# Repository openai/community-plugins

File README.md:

# Community Plugins

A public, Git-backed marketplace of Codex plugins that developers, prospects,
and enterprise teams can inspect before they install. Each plugin is packaged
with its manifest, setup guide, tests, and license or third-party notices.

The CDE team stewards this collection of public plugins for enterprise use
cases. CDE maintainers review contributions and provide support through
repository issues on a best-effort basis; this
repository does not provide an enterprise support commitment or service-level
agreement.

Inclusion in OpenAI's official Plugins Directory requires a separate review. See
[OpenAI's plugin packaging docs](https://developers.openai.com/plugins/build/plugins)
for the distinction between public directory publishing and repo marketplaces.

## Add it to Codex

In Codex, choose **Add plugin marketplace** and use a repository slug or clone
URL, not a raw `marketplace.json` URL:

```text
Source: tonyloehr/community-plugins
Git ref: main
Sparse paths:
.agents/plugins
plugins
```

Those two sparse paths load the complete plugin catalog without pulling the
top-level test suites or demo media. Package-owned source, contract fixtures,
licenses and build receipts remain included. To fetch every repository file,
leave **Sparse paths** blank. To fetch only Grafana Observability, use these two
paths instead:

```text
.agents/plugins
plugins/grafana-observability
```

To fetch only ReviewOps Auditor + Benchmark, use:

```text
.agents/plugins
plugins/reviewops-auditor-benchmark
```

To fetch only React Native to SwiftUI, use:

```text
.agents/plugins
plugins/react-native-to-swiftui
```

To fetch only Autodesk Fusion interoperability, use:

```text
.agents/plugins
plugins/autodesk-fusion
```

To fetch the Physical Engineering candidate, use:

```text
.agents/plugins
plugins/physical-engineering
```

Adding a marketplace makes its catalog available to browse. It does **not**
install, enable, or authenticate every plugin. After adding it, install only
the plugin you want.

The same flow from the CLI:

```sh
# Load the full catalog efficiently.
codex plugin marketplace add tonyloehr/community-plugins \
  --ref main \
  --sparse .agents/plugins \
  --sparse plugins

# Install one plugin from that catalog.
codex plugin add grafana-observability@community-plugins

# Or install the offline ReviewOps package.
codex plugin add reviewops-auditor-benchmark@community-plugins

# Or install the bounded native-migration workflow.
codex plugin add react-native-to-swiftui@community-plugins

# Or install the Fusion interoperability preview (starts in synthetic fixture mode).
codex plugin add autodesk-fusion@community-plugins

# Or install the reusable mechanical CAD workflow and examples.
codex plugin add physical-engineering@community-plugins
```

If you want a full checkout instead of a sparse one:

```sh
codex plugin marketplace add tonyloehr/community-plugins --ref main
```

The `@community-plugins` selector comes from the top-level `name` in
[the marketplace manifest](.agents/plugins/marketplace.json), not from the
GitHub URL. Start a new Codex task after installation so its skills and tools
are picked up.

## Available plugins

| Plugin                                                                         | Purpose                                                                                                                    | Learn more                                                                                                                |
| ------------------------------------------------------------------------------ | -------------------------------------------------------------------------------------------------------------------------- | ------------------------------------------------------------------------------------------------------------------------- |
| [Grafana Observability](plugins/grafana-observability/README.md)               | Inspect administrator-approved, read-only Grafana evidence for infrastructure, APM, logs, IoT/edge, and business KPIs.     | [Guide](plugins/grafana-observability/README.md) · [23-second demo](docs/media/grafana-production-monitoring-demo-8x.mp4) |
| [ReviewOps Auditor + Benchmark](plugins/reviewops-auditor-benchmark/README.md) | Normalize sanitized review-run exports, audit evaluation validity, benchmark lanes, and emit shadow-only guidance offline. | [Guide](plugins/reviewops-auditor-benchmark/README.md)                                                                    |
| [React Native to SwiftUI](plugins/react-native-to-swiftui/README.md)           | Plan a bounded React Native/Expo feature migration, then port one explicitly approved slice with deterministic SwiftUI parity checks. | [Guide](plugins/react-native-to-swiftui/README.md) |
| [Autodesk Fusion](plugins/autodesk-fusion/README.md) | Connect typed CAD/CAM operations, scoped Autodesk data, reviewed cloud recipes and engineering evidence; live qualification required. | [Guide](plugins/autodesk-fusion/README.md) |
| [Physical Engineering](plugins/physical-engineering/README.md) | Build mechanical CAD from a brief, measure exports, preserve revisions and deliver a repeatable handoff. Custom parts plus a drone assembly example. Preview. | [Guide](plugins/physical-engineering/README.md) · [Two-minute demo](docs/media/physical-engineering/README.md) · [Session runbook](docs/physical-engineering-demo-runbook.md) |
| [PCBA Engineering](plugins/pcba-engineering/README.md) | Reconcile assembly data, apply bounded revisions, and independently verify an offline PCBA handoff. | [Guide](plugins/pcba-engineering/README.md) · [2:27 demo](docs/media/pcba-engineering/README.md) |
| [AI/ML API](plugins/aimlapi/README.md) | Choose models and build chat, media, speech, batch, webhook and sandbox integrations with 13 upstream skills. | [Guide](plugins/aimlapi/README.md) |

Grafana Observability requires Codex and Node.js 22.19 or newer. Its manifest
declares both `Read` and `Write`. `Write` is limited to
plugin-owned local audit and evidence files; it does not write to Grafana,
datasources, dashboards, services, or deployments.

Its default startup uses a credential-free fixture, so you can verify the
install without touching a Grafana instance:

```text
Use $setup-grafana-observability to check the fixture profile and available packs.
```

ReviewOps Auditor + Benchmark requires Codex and Node.js 22.19 or newer. Its
manifest declares only `Read`; it has no app, MCP server, authentication,
network call, model replay, workflow execution, or writeback path. Its first
run is also synthetic and credential-free:

```text
Use $normalize-review-runs on the bundled synthetic fixture only. Explain the normalization summary, provenance checks, safety boundaries, and next safe step.
```

React Native to SwiftUI requires Codex and Node.js 22.19 or newer. Its
manifest declares both `Read` and `Write`: planning is read-only, while
writes are limited to an explicitly approved target directory for one feature
slice. It has no app or MCP dependency, does not copy source or assets into
the plugin, and does not promise App Store approval. Its first run is a
read-only parity-planning prompt:

```text
Use $plan-react-native-port to inspect only the declared React Native feature and propose a SwiftUI parity contract. Do not edit files yet.
```

Autodesk Fusion requires Codex and Node.js 22.19 or newer. It declares `Read`
and `Write` for scoped desktop changes, local evidence and configured Autodesk
cloud operations. Authentication is `ON_USE`: the initial synthetic fixture
requires no Autodesk account or running Fusion process. Real desktop, cloud and
manufacturing use requires the appropriate license, profile, authority and
independent qualification; installation grants none of these.

```text
Use $setup-autodesk-fusion to check the synthetic fixture and explain the available connection modes. Do not connect to Autodesk or change a real model.
```

Physical Engineering targets macOS arm64 with Python 3.14 and separately
installed Text-to-CAD 0.10.3. It declares `Read` and `Write` for the selected
local study, runtime and handoff. Custom single-solid parts use declared
measurements; the drone assembly is an optional specialized example. Neither
needs a CAD account. Setup downloads public dependencies, and Codex uses the
user's configured model provider. Digital checks do not qualify fabrication.

```text
Use $engineer-subsystem to start a mechanical-part study from my brief in an empty directory. Record supported measurements and unresolved requirements, then build and check the CAD.
```

## Copy-paste Codex prompts

Browse before installing:

```text
Add the Git-backed marketplace from tonyloehr/community-plugins at ref main. Use sparse paths .agents/plugins and plugins. List the available plugins and recommend the best fit for this repository, but do not install or authenticate anything yet.
```

Install one plugin:

```text
If community-plugins is not already configured, add it from tonyloehr/community-plugins at ref main using sparse paths .agents/plugins and plugins/grafana-observability. Install grafana-observability@community-plugins, explain its permissions and authentication policy, and give me the credential-free smoke-test prompt for a new Codex task.
```

Install ReviewOps without private data:

```text
If community-plugins is not already configured, add it from tonyloehr/community-plugins at ref main using sparse paths .agents/plugins and plugins/reviewops-auditor-benchmark. Install reviewops-auditor-benchmark@community-plugins, explain its read-only offline boundary, and give me the synthetic-fixture smoke-test prompt for a new Codex task.
```

Install React Native to SwiftUI with a read-only first run:

```text
If community-plugins is not already configured, add it from tonyloehr/community-plugins at ref main using sparse paths .agents/plugins and plugins/react-native-to-swiftui. Install react-native-to-swiftui@community-plugins, explain its Read and Write boundaries and ON_USE authentication policy, and give me the read-only parity-planning prompt for a new Codex task.
```

Review before adoption:

```text
Review tonyloehr/community-plugins before I install it. Inspect .agents/plugins/marketplace.json, each plugin manifest, declared capabilities, authentication policy, external endpoints, licenses, and setup instructions. Flag anything that needs security or admin review.
```

## Update or remove

```sh
# Refresh the Git-backed marketplace snapshot.
codex plugin marketplace upgrade community-plugins

# Reinstall a plugin after a new version is published.
codex plugin add grafana-observability@community-plugins
codex plugin add reviewops-auditor-benchmark@community-plugins
codex plugin add react-native-to-swiftui@community-plugins
codex plugin add autodesk-fusion@community-plugins

# Remove the configured marketplace source.
codex plugin marketplace remove community-plugins
```

For an enterprise fork or private mirror, use its HTTPS or SSH clone URL and
make sure Git credentials already work non-interactively. Keep the same
`.agents/plugins/marketplace.json` and `plugins/<name>/` layout.

## Repository layout

Plugin master suites follow `npm run test:<plugin-name>` and are discovered by
`npm run test:marketplace`. Fusion's companion tests live under
[`tests/autodesk-fusion`](tests/autodesk-fusion/README.md), grouped into unit,
integration and security checks. The cold package suite needs no development
dependencies; the full master also rebuilds and runs the deeper Node/Python
contracts:

```sh
npm run test:autodesk-fusion:package
npm --prefix plugins/autodesk-fusion ci --ignore-scripts
npm run test:autodesk-fusion
```

Python 3.12 or newer is required for Fusion's development contract suite, not
for normal Codex startup. The test guide distinguishes synthetic, licensed,
installed-client and native-credential checks; a skipped gate is not a pass.

```text
.agents/plugins/marketplace.json      # Catalog and install policy
plugins/<plugin-name>/                 # One installable plugin
  .codex-plugin/plugin.json            # Required plugin manifest
  README.md                            # Cold-start setup and safety guidance
tests/<plugin-name>/                   # Plugin-specific verification
scripts/                               # Marketplace and package checks
```

## Trust and contributions

Treat every plugin as code you are choosing to run. Review its manifest,
capabilities, authentication policy, setup guide, and license before installing
it. This repository never needs credentials committed to it.

See [CONTRIBUTING.md](CONTRIBUTING.md) to add or update a plugin,
[SECURITY.md](SECURITY.md) to report a vulnerability, and
[CODE_OF_CONDUCT.md](CODE_OF_CONDUCT.md) for participation expectations. The
repository is Apache-2.0 licensed; individual plugins may carry their own
license and third-party notices.

External contributions use pull requests from forks. CDE code owners review
the latest changes, and contributions must satisfy the CLA, test, and security
requirements before merging. Maintainers follow the
[repository access and merge policy](docs/maintainer-guide.md).

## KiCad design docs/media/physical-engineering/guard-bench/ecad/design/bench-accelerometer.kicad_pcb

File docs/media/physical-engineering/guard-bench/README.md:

# Rebuild the guard-coupon bench

An indoor 65 mm quad has two candidate guard walls, 1.00 and 1.40 mm. This companion includes the revised aircraft, two separate printable specimens, a keyed test fixture and a custom three-axis recorder. The nominal tip-to-stop displacement is 2.00 mm for either specimen. Build the virtual station, then compare the enclosure, board and fixture in their installed positions. Measuring acceleration or ring-down requires physical hardware.

## Present the demo

Play the [silent 6:24 stage film](https://github.com/user-attachments/assets/fb31f2b8-419d-4036-bfda-f1f37bc846d7) and follow the [timed reader](presenting/Presenter-runbook.html) on a second screen. Download the HTML reader for its rehearsal controls, or use the [printable PDF](presenting/Presenter-runbook.pdf) and [Markdown script](presenting/Presenter-runbook.md). The narrated edition is on [PR #61](https://github.com/openai/community-plugins/pull/61). Download and open the [standalone HTML prompt deck](presenting/Prompt-runbook.html) for the copy buttons, or use the [plain-text prompts](presenting/Prompt-runbook.md).

A separate 561-second Desktop turn started with an empty output directory and authored its own accelerometer PCB. Its J1.3–U1.6 SDA route measured 5.1534 mm on front copper with zero vias. KiCad reported zero ERC findings, DRC findings, unconnected items and schematic-parity findings. The reviewed film board takes 7.393 mm and two vias between the same pins. The source replay below reproduces the reviewed board. [Independent Desktop board readback](evidence/desktop-board.json)

## Replay from editable source

Start at the repository root. The replay creates a new directory. It generates the populated board from its native KiCad project, uses that fresh STEP for the housing and combines the delivered housing and fixture. Each of the three Physical Engineering handoffs also rebuilds from its own source in a second directory. Set up the CAD runtime with Python 3.14 and uv once. [Physical Engineering setup](../../../../plugins/physical-engineering/references/assembly-designs.md)

```sh
export PE_RUNTIME="${PE_RUNTIME:-$HOME/.cache/physical-engineering/runtime}"
if [ ! -x "$PE_RUNTIME/bin/python" ]; then
  python3 plugins/physical-engineering/scripts/engineering.py setup --runtime "$PE_RUNTIME"
fi

companion=docs/media/physical-engineering/guard-bench
docker build -t physical-engineering-kicad:9.0.2 "$companion/ecad"
python3 "$companion/replay.py" ./guard-bench-replay --kicad-image physical-engineering-kicad:9.0.2
```

A native KiCad 9.0.2 installation with matching stock symbol/footprint libraries, `kicad-cli` on PATH and Python bindings for `pcbnew` also works with the same command after removing the image argument. If necessary, set `KICAD_PYTHON` to the interpreter containing `pcbnew`. The Docker run uses the local image with networking disabled after setup. The final `replay.json` contains the results and baseline/rebuild manifest digests.

| Output under the replay directory | What to open |
| --- | --- |
| `aircraft/` | Complete STEP, colored GLB, print meshes, offline viewer, formatted aircraft/bench BOM, board guide and flight-controller thickness readback |
| `board/` | Native project with local models, rendered schematic PDF, ERC, parity-aware DRC, netlist, placements, parts list, nine Gerber layers, plated/non-plated drills and populated STEP |
| `fixture/` | Assembly with one 1.00 mm specimen, keyed stop and an enclosure reference. The alternate directory contains the installed 1.40 mm specimen and its separate print. |
| `housing/` | Enclosure positioned around the freshly exported, populated recorder. The installed board contains discrete substrate, copper, pad, via and packaged-part geometry. |
| `station/` | Integrated STEP, GLB and a registration report. The real recorder assembly replaces the two enclosure reference bodies. |
| `aircraft-rebuild/`, `fixture-rebuild/`, `housing-rebuild/` | Independent rebuilds from each handoff’s delivered source |
| `housing-regression/exports/integration.json` | Rejected enclosure copy with the earlier 15 × 3 mm opening. The cable gauge intersects 28.70 mm³ of the wall. |
| `board/edge-regression-drc.json` | Separate rejected source copy with the connector moved 0.25 mm toward the edge |

The [full system workbook](sourcing/system-bom.xlsx) consolidates aircraft, both specimen configurations, the recorder PCB and workshop equipment. Its six sheets reconcile 69 source entries into 59 distinct rows. The two coupon columns represent alternative assemblies and shared fixture fasteners are counted once. [Flat CSV](sourcing/system-bom.csv) · [Reconciliation](sourcing/reconciliation.json)

## Engineering decisions

| Interface | Source decision and digital evidence | Physical work |
| --- | --- | --- |
| Aircraft controller | The BETAFPV Air 5IN1 specifies a 0.80 mm substrate. The earlier STEP measured 0.95 mm. The revised model holds the lower face at Z 3.50 mm and seats its upper components at 4.30 mm. | Check the received revision, compressed grommets, screw engagement and harness routing. [Controller specification](https://betafpv.com/products/air-brushless-flight-controller?variant=41142912745606) |
| Motor connection | The 0702SE II leads ship with connectors. The selected controller takes soldered motor wires. The workbook records lead termination and kit inclusions. | Confirm finished lengths, strain relief, prop fit and propulsion load. [Motor specification](https://betafpv.com/products/0702-ii-brushless-motors?variant=41478718750854) |
| Recorder board | An ST LIS3DHTR and side-entry JST SH connector share the 34 × 22 mm board. A 3.3 V host supplies power and reads I²C at address 0x18. The two-layer SDA route from J1.3 to U1.6 measures 7.393 mm and changes layers twice. | Fabricate, inspect orientation and electrical joints, verify identity and gravity response. [ST datasheet](https://www.st.com/resource/en/datasheet/lis3dh.pdf) · [JST drawing](https://www.jst-mfg.com/product/pdf/eng/eSH.pdf) |
| Connector hold-downs | KiCad requires 0.50 mm copper-to-edge clearance. Moving J1 inward 0.25 mm gives both hold-down pads 0.60 mm. The replay moves J1 back in a copy and requires both 0.35 mm violations. Moving an already-routed footprint also triggers other layout findings recorded in that copy. | Check actual fit and fabrication tolerances. |
| Recorder mounting | The housing uses a 64 mm ear spacing and checks the populated board against the lid, four mounts, screws and cable entry. A rectangular insertion gauge models approach to the header exterior. | Check the keyed mating plug, slack, strain relief, physical lid removal and mounting stiffness. |
| Guard experiment | Both coupons use the same locating features, 16.30 mm inner radius and 2.00 mm nominal travel. The installed station uses the baseline coupon and includes the alternate separately. | Print both in the same material and orientation, measure the seated gaps, alternate specimens across repeated trials and record the instrument response. |

[Aircraft sourcing workbook](sourcing/whoop-sourcing.xlsx) · [Aircraft sourcing CSV](sourcing/whoop-sourcing.csv) · [Dated supplier evidence](sourcing/source-receipts.json) · [Custom PCB procurement](sourcing/accelerometer-parts.csv)

The aircraft procurement ledger covers all 20 aircraft and 14 bench lines. The recorder BOM contains seven fitted components across five part numbers. The manufacturer listed the selected aircraft controller and motor variants as unavailable at the sourcing review on November 28, 2026 UTC. The ledger identifies alternate supplier listings and distinguishes a store pack from quantity installed. Recheck availability and variant before ordering.

## Source and evidence

The [aircraft](designs/aircraft/), [from-empty fixture](designs/fixture/) and [enclosure](designs/housing/) hold editable geometry and independent checks. The [native KiCad sources](ecad/design/) contain the electrical design. Extract [models.zip](ecad/models.zip) into the `ecad` directory of a working copy to open the native project with its component solids. The original library notices and modifications are documented in [attribution](ecad/ATTRIBUTION.md).

The [earlier controller readback](evidence/controller-substrate.json) compares the exported 0.95 and 0.80 mm solids. The [original preflight DRC](evidence/original-preflight-drc.json) records the two hold-down failures on the initial PCB layout. The source replay independently recreates these edge errors on a copy of the final routed board.

The three handoffs passed 37 aircraft, 33 fixture and 19 housing export checks. Their design-specific checks add seven controller substrate and seating checks, 26 drawing checks across both coupons and 12 board-to-case checks. The registered station has zero measured plate-to-case interference. The populated board has 5.505 mm lid clearance. A separate rectangular gauge extending as far as the molded connector mouth overlaps a tab by 0.0046 mm³, so the keyed mating plug still requires a physical trial.

Reference qualification used KiCad 9.0.2 on Debian 13 arm64 and macOS arm64 with Python 3.14.6, build123d 0.13.0 and Text-to-CAD 0.10.3. The [replay evidence](evidence/replay.json) records this run. Native STEP headers can contain export times. Each handoff’s manifest records the plugin's artifact and geometric comparisons.

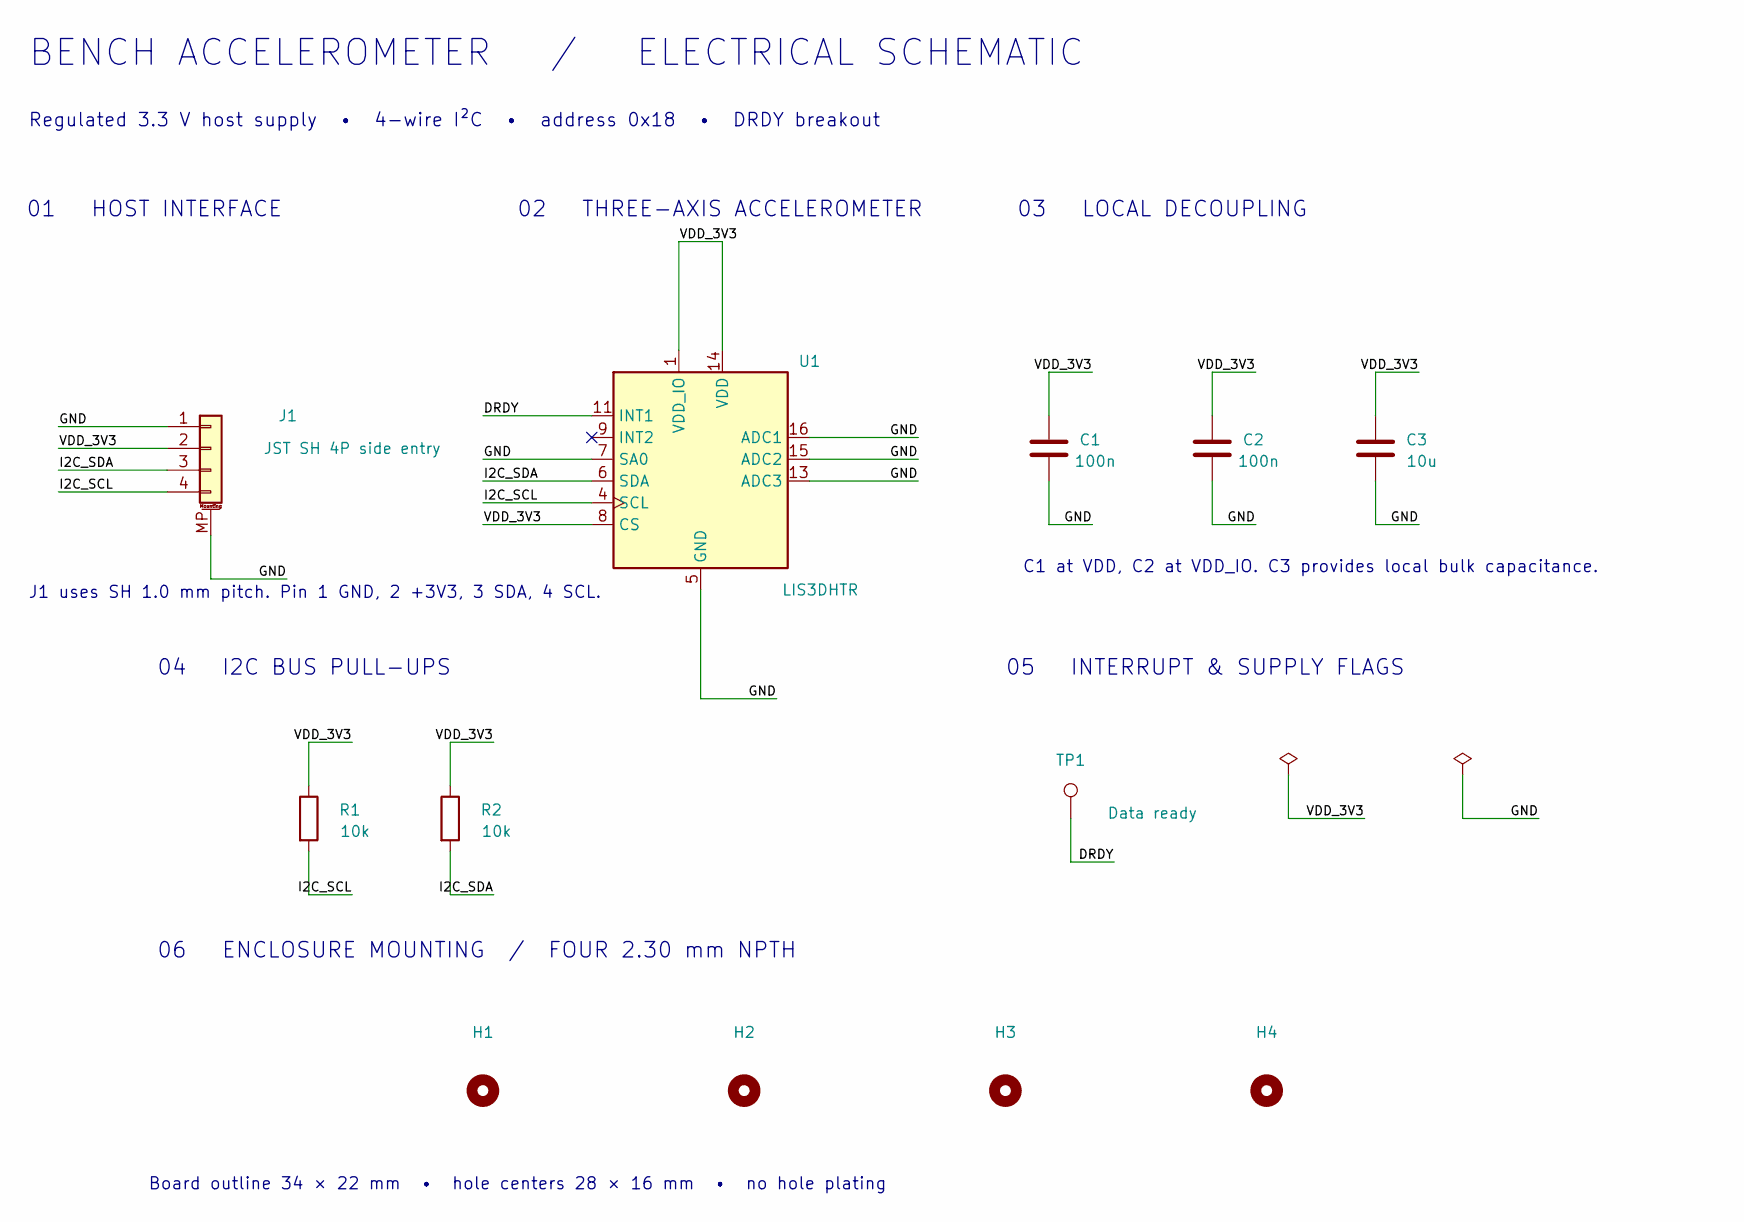
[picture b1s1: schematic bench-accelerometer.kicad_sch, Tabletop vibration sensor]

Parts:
C1, C2: 100n; C_0603_1608Metric; MPN GRM188R71C104KA01D
C3: 10u; C_0805_2012Metric; MPN GRM21BR61A106KE19L
H1, H2, H3, H4: 2.30 mm NPTH; MountingHole_2.30mm_M2
J1: JST SH 4P side entry; JST_SH_SM04B-SRSS-TB_1x04-1MP_P1.00mm_Horizontal; MPN SM04B-SRSS-TB(LF)(SN)
R1, R2: 10k; R_0603_1608Metric; MPN RC0603FR-0710KL
TP1: Data ready; TestPoint_Pad_D1.5mm
U1: LIS3DHTR; LGA-16_3x3mm_P0.5mm_LayoutBorder3x5y; MPN LIS3DHTR

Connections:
/DRDY: TP1.1, U1.11 (INT1)
/GND: C1.2, C2.2, C3.2, J1.1, J1.MP (MountPin), U1.5 (GND), U1.7 (SA0), U1.10 (GND), U1.12 (GND), U1.13 (ADC3), U1.15 (ADC2), U1.16 (ADC1)
/I2C_SCL: J1.4, R1.2, U1.4 (SCL)
/I2C_SDA: J1.3, R2.2, U1.6 (SDA)
/VDD_3V3: C1.1, C2.1, C3.1, J1.2, R1.1, R2.1, U1.1 (VDD_IO), U1.8 (CS), U1.14 (VDD)

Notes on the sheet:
01 HOST INTERFACE
02 THREE-AXIS ACCELEROMETER
03 LOCAL DECOUPLING
04 I2C BUS PULL-UPS
05 INTERRUPT & SUPPLY FLAGS
06 ENCLOSURE MOUNTING / FOUR 2.30 mm NPTH
BENCH ACCELEROMETER / ELECTRICAL SCHEMATIC
Regulated 3.3 V host supply • 4-wire I²C • address 0x18 • DRDY breakout
J1 uses SH 1.0 mm pitch. Pin 1 GND, 2 +3V3, 3 SDA, 4 SCL.
C1 at VDD, C2 at VDD_IO. C3 provides local bulk capacitance.
Board outline 34 × 22 mm • hole centers 28 × 16 mm • no hole plating

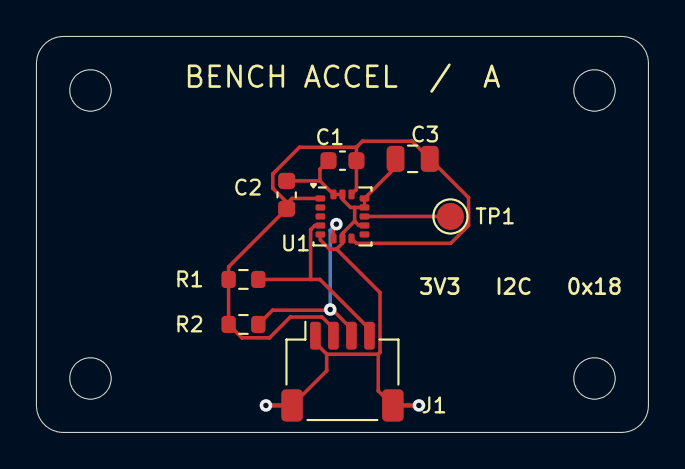
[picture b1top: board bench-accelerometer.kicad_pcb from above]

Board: 2 copper layers, 34.0 x 22.0 mm, 12 parts (0 on the bottom side), 5 nets.

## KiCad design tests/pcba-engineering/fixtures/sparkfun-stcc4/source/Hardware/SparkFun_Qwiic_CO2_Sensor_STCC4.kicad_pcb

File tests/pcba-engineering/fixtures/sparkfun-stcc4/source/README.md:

# SparkFun CO2 Sensor - STCC4/SHT41 (Qwiic)

The SparkFun CO2 Sensor - STCC4/SHT40 (Qwiic) is a compact, plug-and-play air quality breakout built around the STCC4 CO₂ sensor paired with a Sensirion SHT41 temperature and humidity sensor for on-board environmental compensation. Connect via the Qwiic connector or the PTH header (GND, 3V3, SDA, SCL) and start reading calibrated CO₂ concentrations, temperature, and relative humidity over I2C in minutes — no external components required.

Designed for our [Qwiic ecosystem](https://www.sparkfun.com/qwiic), this 1" × 1" board plugs straight into any Qwiic-enabled microcontroller. A power LED confirms operation at a glance, and the four mounting holes make permanent installation straightforward. Whether you are monitoring indoor air quality, building a ventilation controller, or logging CO₂ trends in a greenhouse or classroom, the STCC4 delivers accurate, temperature- and humidity-compensated readings in a breadboard-friendly package.

## Repository Contents

* **/docs** - Documentation files for GitHub pages
* **/Documents** - Datasheets, additional product information
* **/Hardware** - KiCad design files (.kicad_sch, .kicad_pcb)
* **/Production** - Production panel files

## Documentation

* **[Library](https://github.com/sparkfun/SparkFun_STCC4_Arduino_Library)** - Arduino library for the SparkFun CO2 Sensor - STCC4/SHT40 (Qwiic).
* **[Hookup Guide](https://docs.sparkfun.com/SparkFun_CO2_Sensor_STCC4+SHT40/)** - Basic hookup guide for the SparkFun CO2 Sensor - STCC4/SHT40 (Qwiic).

## Product Versions

* **[SEN-31536](https://www.sparkfun.com/sparkfun-co2-sensor-stcc4-sht40-qwiic.htmlX)** - Initial release of the SparkFun CO2 Sensor - STCC4/SHT40 (Qwiic).

## License Information

This product is _**open source**_!

Please review the LICENSE.md file for license information.

If you have any questions or concerns about licensing, please contact technical support on our [SparkFun forums](https://forum.sparkfun.com/viewforum.php?f=152).

Distributed as-is; no warranty is given.

_- Your friends at SparkFun._

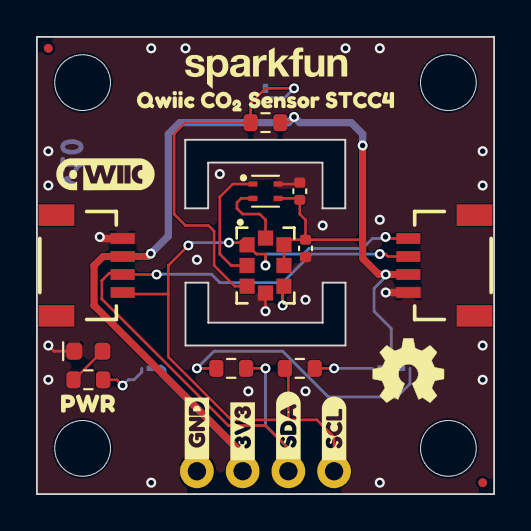
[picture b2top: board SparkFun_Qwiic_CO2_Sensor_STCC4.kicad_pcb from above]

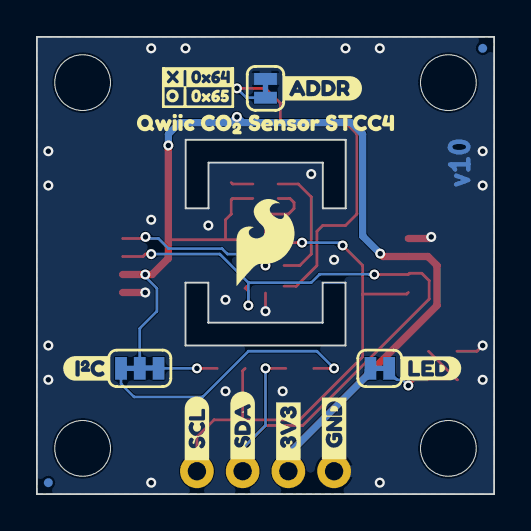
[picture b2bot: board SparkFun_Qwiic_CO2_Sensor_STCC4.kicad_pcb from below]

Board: 2 copper layers, 25.4 x 25.4 mm, 43 parts (16 on the bottom side), 11 nets.

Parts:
C10, C11: 0.1uF; C_0402_1005Metric
D1: Red; LED_0603_1608Metric_Red
FID1, FID2, FID3, FID4: Fiducial_0.5mm; Fiducial_0.5mm_Mask1mm
G4: OSHW_Logo; Creative_Commons_License
J1, J2: Qwiic_RA; JST_1x04_P1.0mm_Horizontal_SMD
J3: Conn_01x06; 1x04_P2.54mm
JP1: LED; Jumper_2_NC_Trace
JP2: I²C; Jumper_3_NC-2_Trace
JP3: ADDR; Jumper_2_NC_Trace
R3, R6: 4.7k; R_0603_1608Metric
R4, R5: 2.2k; R_0603_1608Metric
Ref**: Val**; OSHW_Logo_4mm
ST1, ST2, ST3, ST4: Standoff
U2: STCC4
U3: SHT40; Sensirion_DFN-4_1.5x1.5mm_P0.8mm_SHT4x_NoCentralPad
kibuzzard-6A0B3951: G***; kibuzzard-6A0B3951
kibuzzard-6A0B3970: G***; kibuzzard-6A0B3970
kibuzzard-6A063CE8: G***; kibuzzard-6A063CE8
kibuzzard-6A079B3E, kibuzzard-6A079B3E#2: G***; kibuzzard-6A079B3E
kibuzzard-6A079B36, kibuzzard-6A079B36#2: G***; kibuzzard-6A079B36
kibuzzard-6A07969C: G***; kibuzzard-6A07969C
kibuzzard-689A66E2: G***; kibuzzard-689A66E2
kibuzzard-689A66E9: G***; kibuzzard-689A66E9
kibuzzard-689A66EE: G***; kibuzzard-689A66EE
kibuzzard-689A66F4: G***; kibuzzard-689A66F4
kibuzzard-689A642E: G***; kibuzzard-689A642E
kibuzzard-689A6711: G***; kibuzzard-689A6711
kibuzzard-689A6718: G***; kibuzzard-689A6718
kibuzzard-689A6721: G***; kibuzzard-689A6721
kibuzzard-689A6728: G***; kibuzzard-689A6728
kibuzzard-689A6796: G***; kibuzzard-689A6796

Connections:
3.3V: C10.1, C11.1, J1.2, J2.2, J3.2, JP1.2 (B), JP2.2 (B), R6.2, U2.6 (VDD_IO), U2.7 (VDD), U3.3 (VDD)
ADDR: JP3.2 (B), R6.1, U2.3 (ADDR)
GND: C10.2, C11.2, D1.1 (K), J1.1, J2.1, J3.1, JP3.1 (A), U2.4 (GND), U3.4 (VSS)
unnamed: D1.2 (A), R3.1
unnamed: JP1.1 (A), R3.2
unnamed: JP2.1 (A), R5.1
unnamed: JP2.3 (C), R4.1
unnamed: U2.8 (SCL_C), U3.2 (SCL)
unnamed: U2.2 (SDA_C), U3.1 (SDA)
SCL: J1.4, J2.4, J3.4, R4.2, U2.1 (SCL)
SDA: J1.3, J2.3, J3.3, R5.2, U2.5 (SDA)

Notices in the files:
parts and their libraries:
Released under the Creative Commons Attribution Share-Alike 4.0 License
https://creativecommons.org/licenses/by-sa/4.0
